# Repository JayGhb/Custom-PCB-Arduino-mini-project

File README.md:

# Custom-PCB-Arduino-mini-project
Logging data, collected from custom pcb board, into SD card, using Arduino Pro mini.

The custom PCB is a break-out board for a lux, temperature and a humidity sensor, created with EAGLE 9.1.3
The ICs used are:
  * [TSL2561](https://cdn-shop.adafruit.com/datasheets/TSL2561.pdf) Lux sensor
  * [TMP102](http://www.ti.com/lit/ds/symlink/tmp102.pdf) Temperature sensor
  * [Si7021](https://www.silabs.com/documents/public/data-sheets/Si7021-A20.pdf) Humidity sensor

The project implements two I2C intefaces. The default Arduino Pro mini hardware one and a software I2C inteface using [SoftwareWire](https://github.com/Testato/SoftwareWire) with pins (8,9) as SDA, SCL respectively.

## JASON_TSL2561
A custom modification of the [Adafruit tsl2561 library](https://github.com/adafruit/TSL2561-Arduino-Library) is also implemented under
the JASON_TSL2561 folder, to be able to use the convenient provided functions with the SoftwareWire library.

### Other parts used
  1. Arduino Pro mini
  1. [MicroSD breakout board](https://www.sparkfun.com/products/544?_ga=2.162410361.45600573.1549733271-2101103923.1549733271)
  
Image of the board before ratsnest:

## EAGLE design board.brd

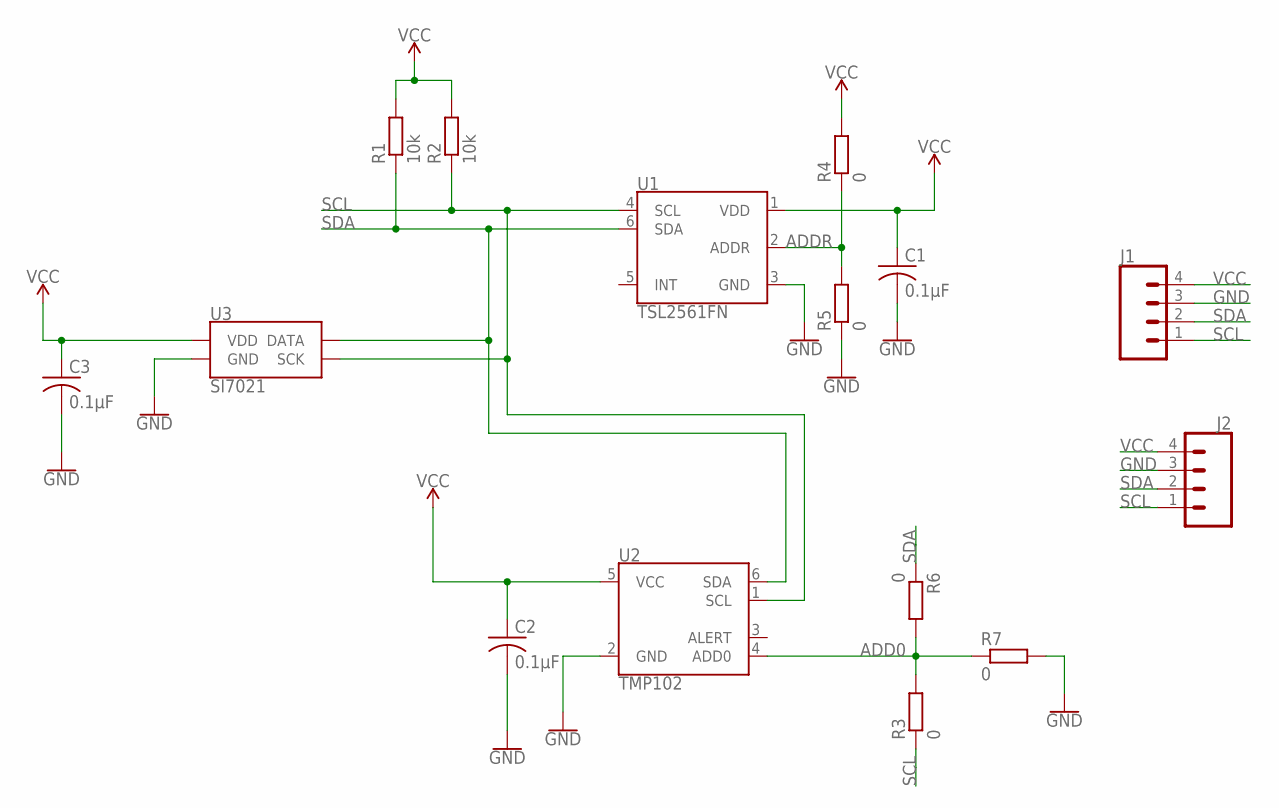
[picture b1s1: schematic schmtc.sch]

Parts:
C1, C2, C3: 0.1μF; C0603
J1, J2: CONN_04; 1X04
R1, R2: 10k; R0603
R3, R4, R5, R6, R7: 0; R0603
U1: TSL2561FN; DFN-6-2X2
U2: TMP102; SOT563
U3: SI7021; DFN-6-3X3-SI7021

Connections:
ADD0: R3.2, R6.2, R7.1, U2.4 (ADD0)
ADDR: R4.1, R5.2, U1.2 (ADDR)
GND: C1.2, C2.2, C3.2, J1.3, J2.3, R5.1, R7.2, U1.3 (GND), U2.2 (GND), U3.GND
SCL: J1.1, J2.1, R2.1, R3.1, U1.4 (SCL), U2.1 (SCL), U3.SCK
SDA: J1.2, J2.2, R1.1, R6.1, U1.6 (SDA), U2.6 (SDA), U3.DATA
VCC: C1.1, C2.1, C3.1, J1.4, J2.4, R1.2, R2.2, R4.2, U1.1 (VDD), U2.5 (VCC), U3.VDD

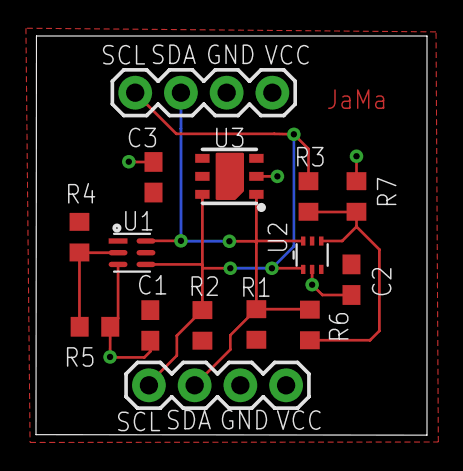
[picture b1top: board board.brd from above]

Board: 2 copper layers, 21.7 x 22.2 mm, 15 parts (0 on the bottom side), 6 nets.

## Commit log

2019-10-01 Add license text

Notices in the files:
parts and their libraries:
SparkFun-Connectors: Licensing: Creative Commons ShareAlike 4.0 International - https://creativecommons.org/licenses/by-sa/4.0
